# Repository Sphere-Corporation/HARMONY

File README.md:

<div align="center">
  
</div>

Project Harmony

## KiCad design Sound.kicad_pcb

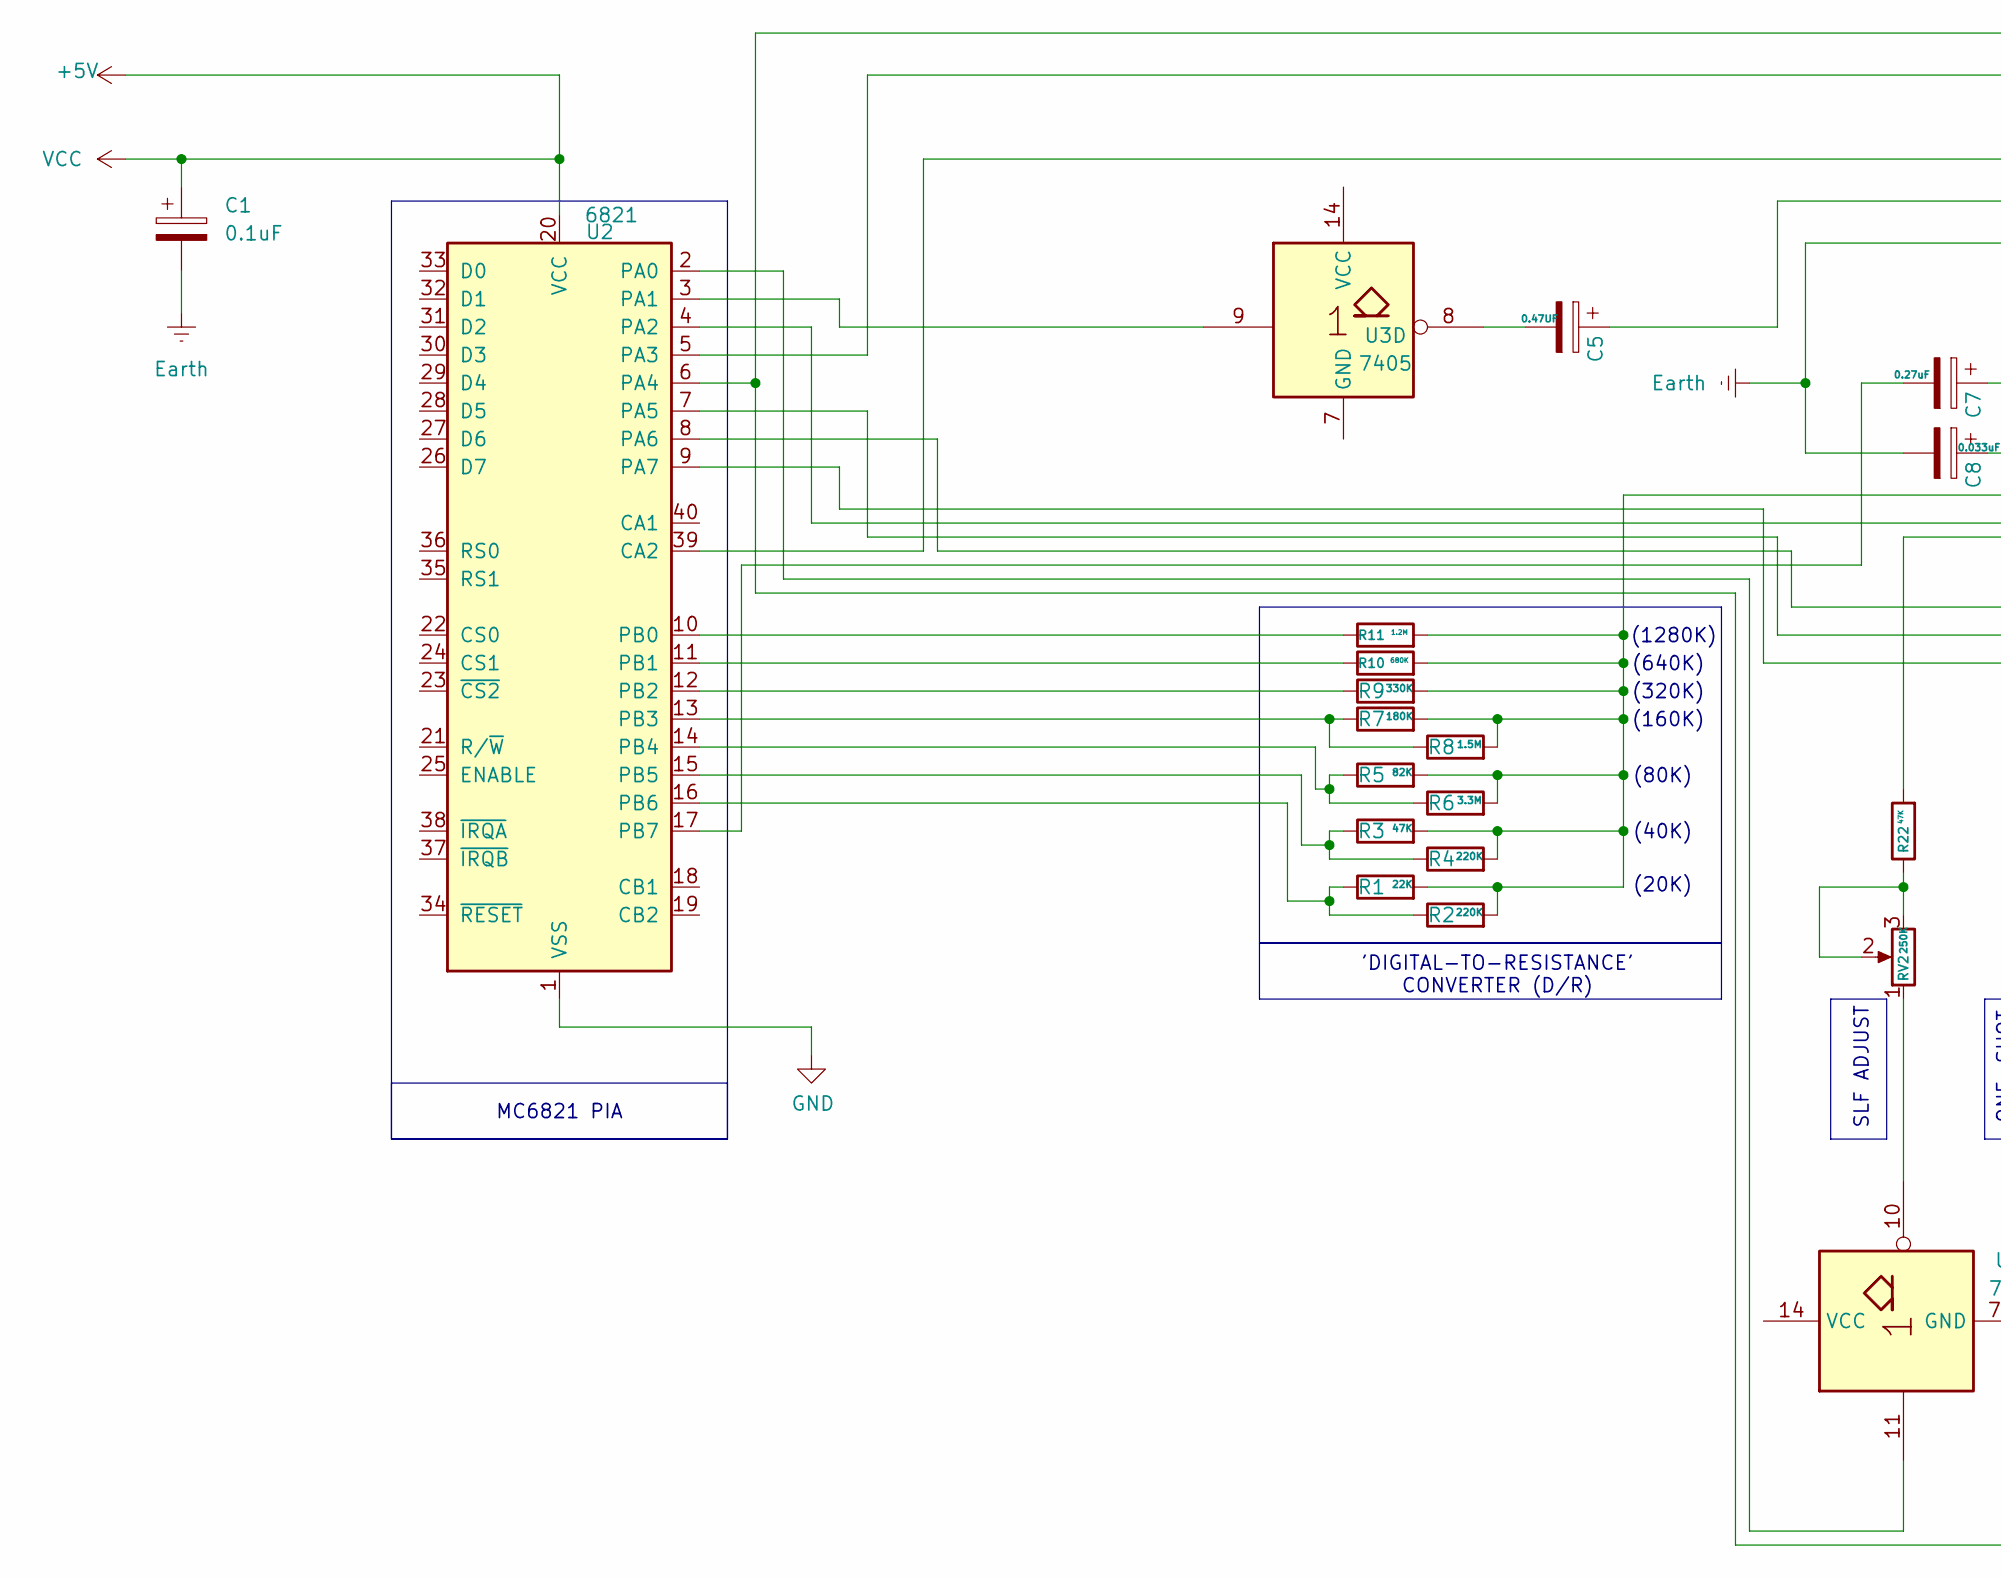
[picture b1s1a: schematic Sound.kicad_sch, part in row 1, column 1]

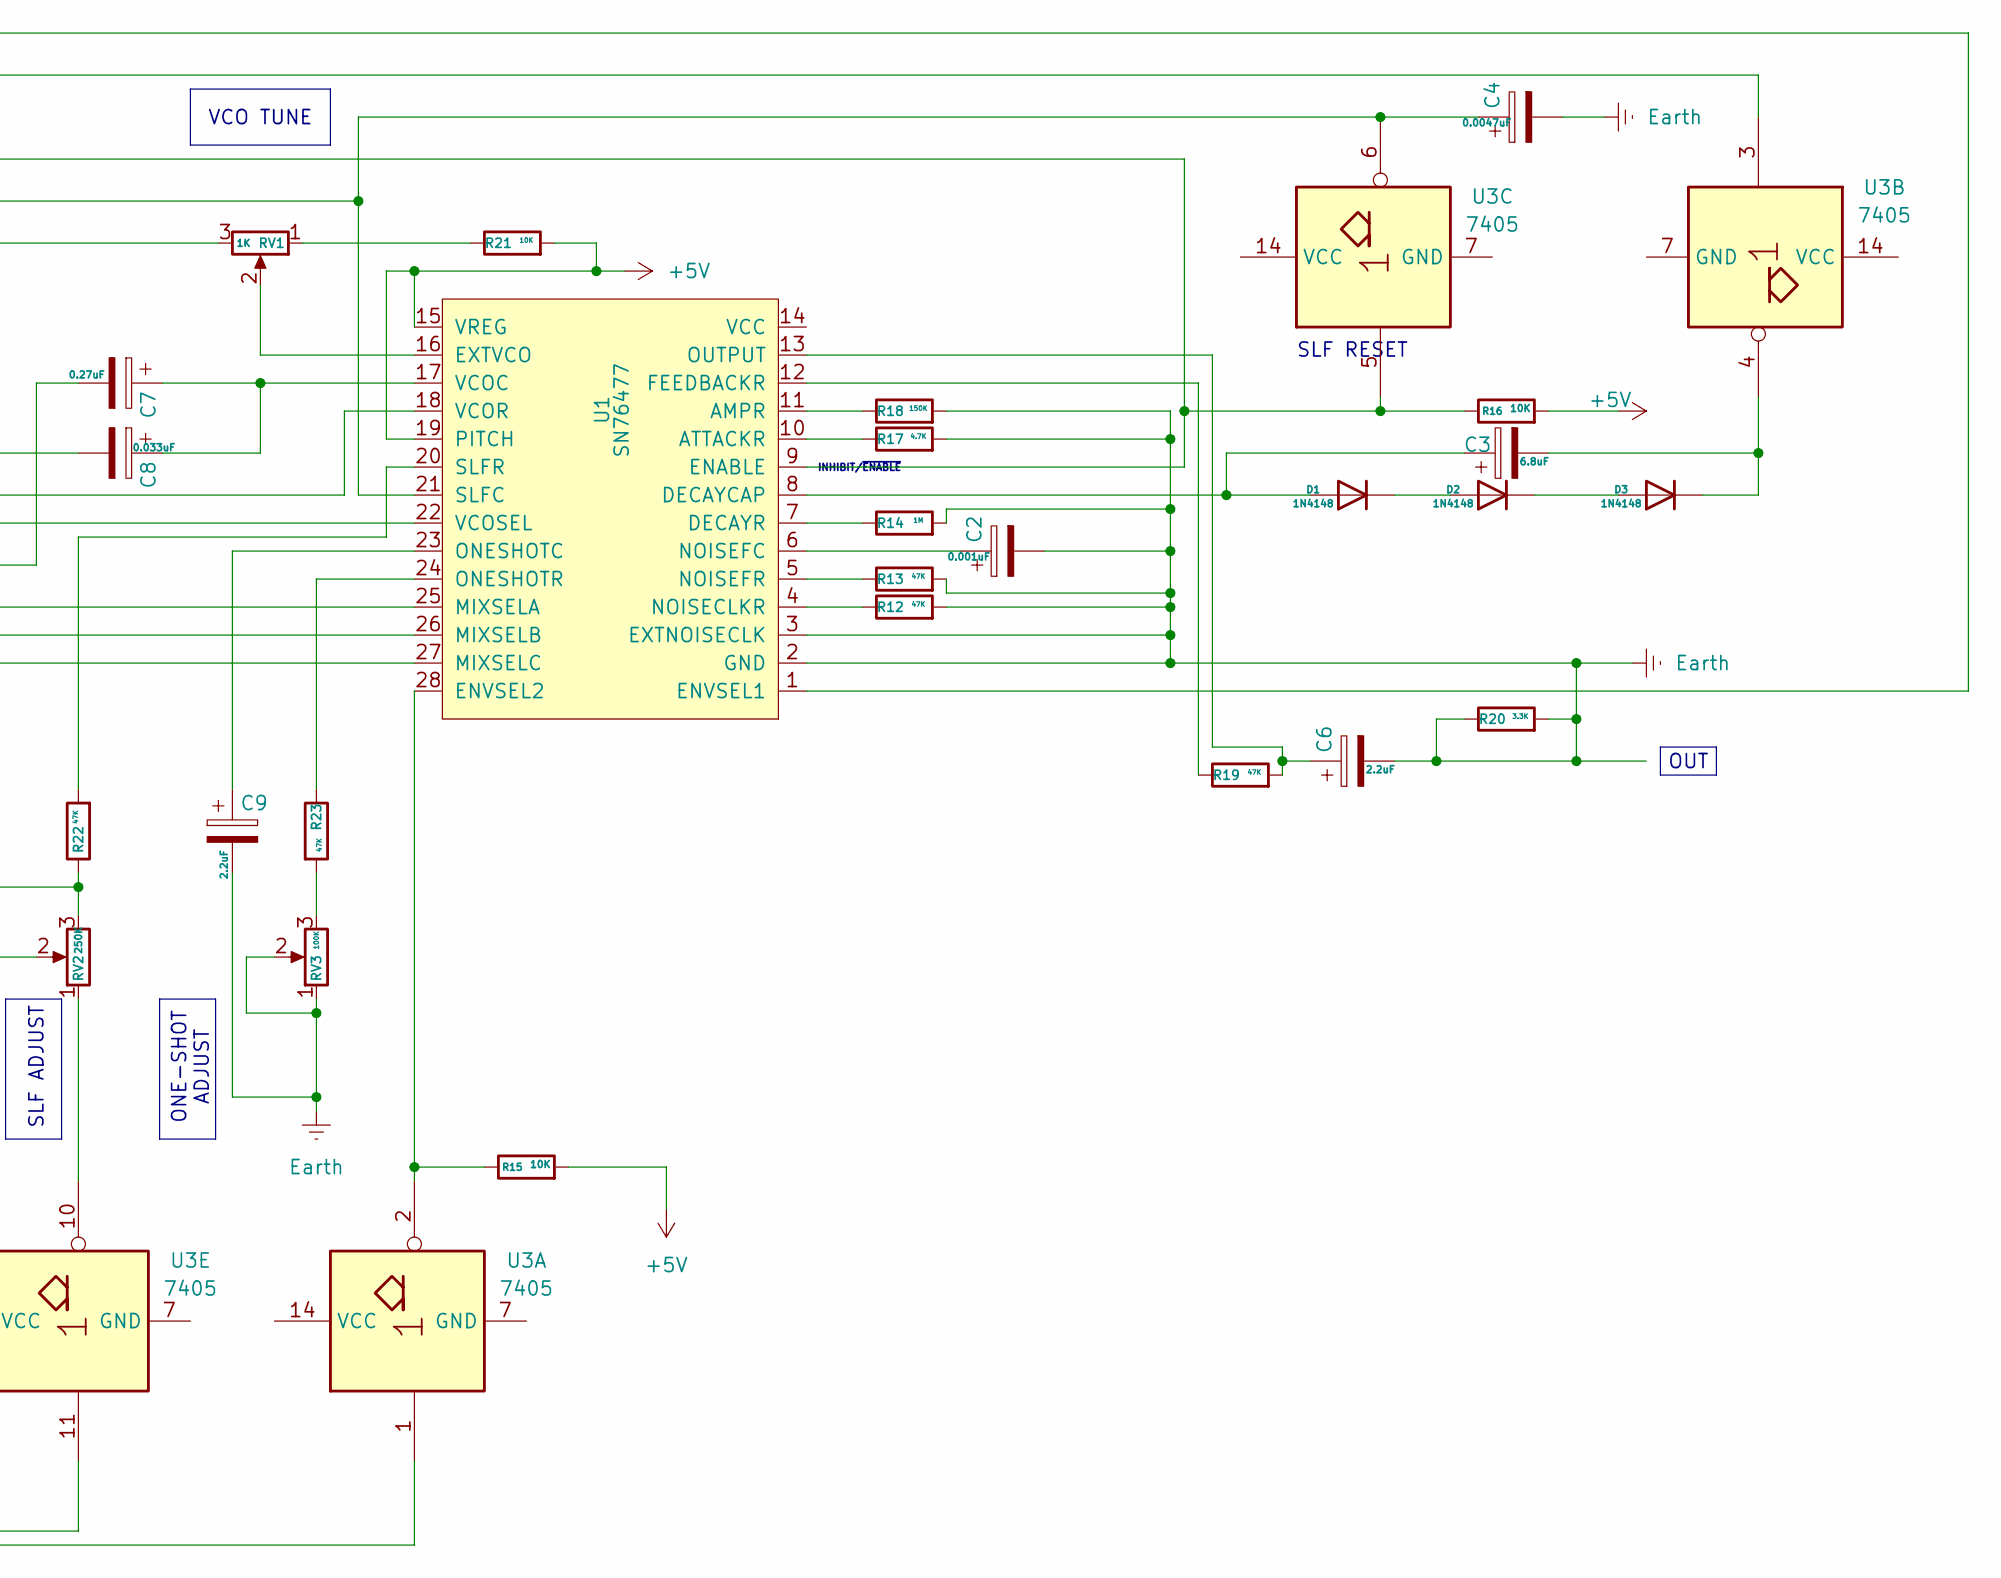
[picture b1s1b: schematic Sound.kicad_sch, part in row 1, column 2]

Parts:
C1: 0.1uF; CP_Radial_Tantal_D8.0mm_P2.50mm
C2: 0.001uF; CP_Radial_Tantal_D8.0mm_P2.50mm
C3: 6.8uF; CP_Radial_Tantal_D7.0mm_P5.00mm
C4: 0.0047uF; CP_Radial_Tantal_D8.0mm_P2.50mm
C5: 0.47UF; CP_Radial_Tantal_D8.0mm_P2.50mm
C6, C9: 2.2uF; CP_Radial_Tantal_D8.0mm_P2.50mm
C7: 0.27uF; CP_Radial_Tantal_D8.0mm_P2.50mm
C8: 0.033uF; CP_Radial_Tantal_D8.0mm_P2.50mm
D1, D2, D3: 1N4148; D_DO-35_SOD27_P7.62mm_Horizontal
R1: 22K; R_Axial_DIN0204_L3.6mm_D1.6mm_P7.62mm_Horizontal
R2, R4: 220K; R_Axial_DIN0204_L3.6mm_D1.6mm_P7.62mm_Horizontal
R3, R12, R13, R19, R22, R23: 47K; R_Axial_DIN0204_L3.6mm_D1.6mm_P7.62mm_Horizontal
R5: 82K; R_Axial_DIN0204_L3.6mm_D1.6mm_P7.62mm_Horizontal
R6: 3.3M; R_Axial_DIN0204_L3.6mm_D1.6mm_P7.62mm_Horizontal
R7: 180K; R_Axial_DIN0204_L3.6mm_D1.6mm_P7.62mm_Horizontal
R8: 1.5M; R_Axial_DIN0204_L3.6mm_D1.6mm_P7.62mm_Horizontal
R9: 330K; R_Axial_DIN0204_L3.6mm_D1.6mm_P7.62mm_Horizontal
R10: 680K; R_Axial_DIN0204_L3.6mm_D1.6mm_P7.62mm_Horizontal
R11: 1.2M; R_Axial_DIN0204_L3.6mm_D1.6mm_P7.62mm_Horizontal
R14: 1M; R_Axial_DIN0204_L3.6mm_D1.6mm_P7.62mm_Horizontal
R15, R16, R21: 10K; R_Axial_DIN0204_L3.6mm_D1.6mm_P7.62mm_Horizontal
R17: 4.7K; R_Axial_DIN0204_L3.6mm_D1.6mm_P7.62mm_Horizontal
R18: 150K; R_Axial_DIN0204_L3.6mm_D1.6mm_P7.62mm_Horizontal
R20: 3.3K; R_Axial_DIN0204_L3.6mm_D1.6mm_P7.62mm_Horizontal
RV1: 1K; Potentiometer_ACP_CA6-VSMD_Vertical
RV2: 250K; Potentiometer_ACP_CA6-VSMD_Vertical
RV3: 100K; Potentiometer_ACP_CA6-VSMD_Vertical
U1: SN76477; DIP-28_W15.24mm_Socket
U2: 6821; DIP-40_W15.24mm_Socket
U3: 7405; DIP-14_W7.62mm_Socket

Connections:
+5V: C1.1, R15.2, R16.2, R21.2, U1.15 (VREG), U1.19 (PITCH), U2.20 (VCC)
Earth: C1.2, C2.2, C4.2, C6.2, C8.2, C9.2, R12.2, R13.2, R14.2, R17.2, R18.2, R20.1, R20.2, RV1.3, RV3.1, RV3.2, U1.2 (GND), U1.3 (EXTNOISECLK)
GND: U2.1 (VSS)
unnamed: C5.2, U3.8
unnamed: C3.1, D1.2 (A), U1.8 (DECAYCAP)
unnamed: D1.1 (K), D2.2 (A)
unnamed: D2.1 (K), D3.2 (A)
unnamed: C3.2, D3.1 (K), U3.4
unnamed: R21.1, RV1.1
unnamed: R22.1, RV2.2, RV2.3
unnamed: R23.2, RV3.3
unnamed: RV2.1, U3.10
unnamed: R18.1, U1.11 (AMPR)
unnamed: R17.1, U1.10 (ATTACKR)
unnamed: R14.1, U1.7 (DECAYR)
unnamed: R16.1, U1.9 (ENABLE), U2.39 (CA2), U3.5
unnamed: U1.1 (ENVSEL1), U2.6 (PA4), U3.1
unnamed: R15.1, U1.28 (ENVSEL2), U3.2
unnamed: RV1.2, U1.16 (EXTVCO)
unnamed: R19.1, U1.12 (FEEDBACKR)
unnamed: U1.25 (MIXSELA), U2.8 (PA6)
unnamed: U1.26 (MIXSELB), U2.7 (PA5)
unnamed: U1.27 (MIXSELC), U2.9 (PA7)
unnamed: R12.1, U1.4 (NOISECLKR)
unnamed: C2.1, U1.6 (NOISEFC)
unnamed: R13.1, U1.5 (NOISEFR)
unnamed: C9.1, U1.23 (ONESHOTC)
unnamed: R23.1, U1.24 (ONESHOTR)
unnamed: C6.1, R19.2, U1.13 (OUTPUT)
unnamed: C4.1, C5.1, U1.21 (SLFC), U3.6
unnamed: R22.2, U1.20 (SLFR)
unnamed: C7.1, C8.1, U1.17 (VCOC)
unnamed: R1.2, R2.2, R3.2, R4.2, R5.2, R6.2, R7.2, R8.2, R9.2, R10.2, R11.2, U1.18 (VCOR)
unnamed: U1.22 (VCOSEL), U2.4 (PA2)
unnamed: U2.2 (PA0), U3.11
unnamed: U2.3 (PA1), U3.9
unnamed: U2.5 (PA3), U3.3
unnamed: R11.1, U2.10 (PB0)
unnamed: R10.1, U2.11 (PB1)
unnamed: R9.1, U2.12 (PB2)
unnamed: R7.1, R8.1, U2.13 (PB3)
unnamed: R5.1, R6.1, U2.14 (PB4)
unnamed: R3.1, R4.1, U2.15 (PB5)
unnamed: R1.1, R2.1, U2.16 (PB6)
unnamed: C7.2, U2.17 (PB7)

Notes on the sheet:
(1280K)
(160K)
VCO TUNE
INHIBIT/~{ENABLE}
(640K)
(320K)
(80K)
(20K)
MC6821 PIA
SLF RESET
ONE-SHOT ADJUST
OUT
(40K)
SLF ADJUST
'DIGITAL-TO-RESISTANCE' CONVERTER (D/R)

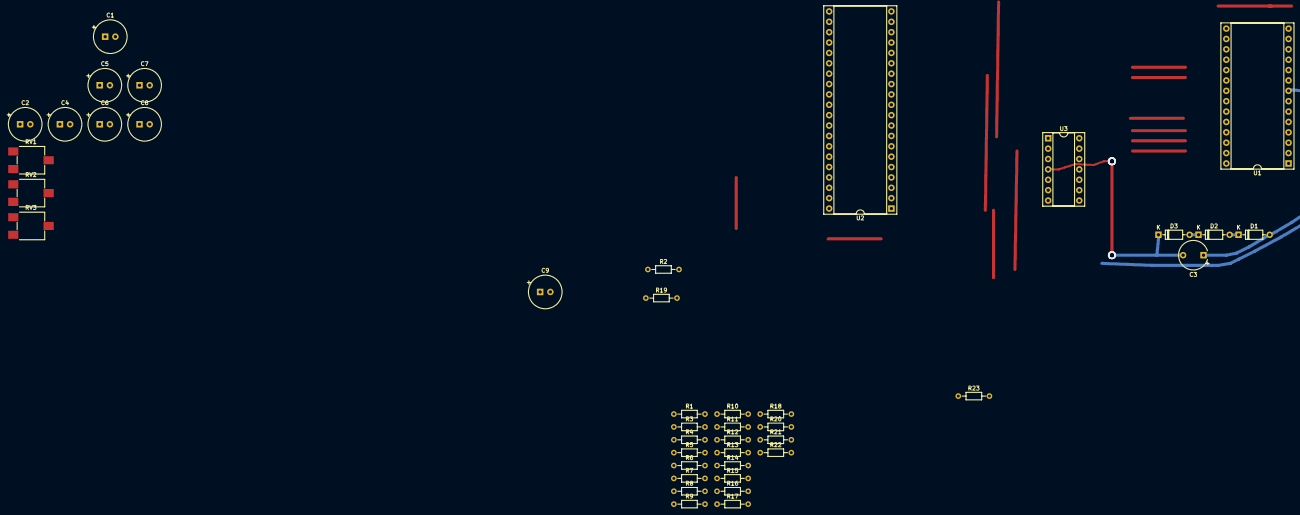
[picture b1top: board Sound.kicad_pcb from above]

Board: 2 copper layers, 41 parts (0 on the bottom side), 44 nets.

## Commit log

2025-06-12 Added some misc reference code
